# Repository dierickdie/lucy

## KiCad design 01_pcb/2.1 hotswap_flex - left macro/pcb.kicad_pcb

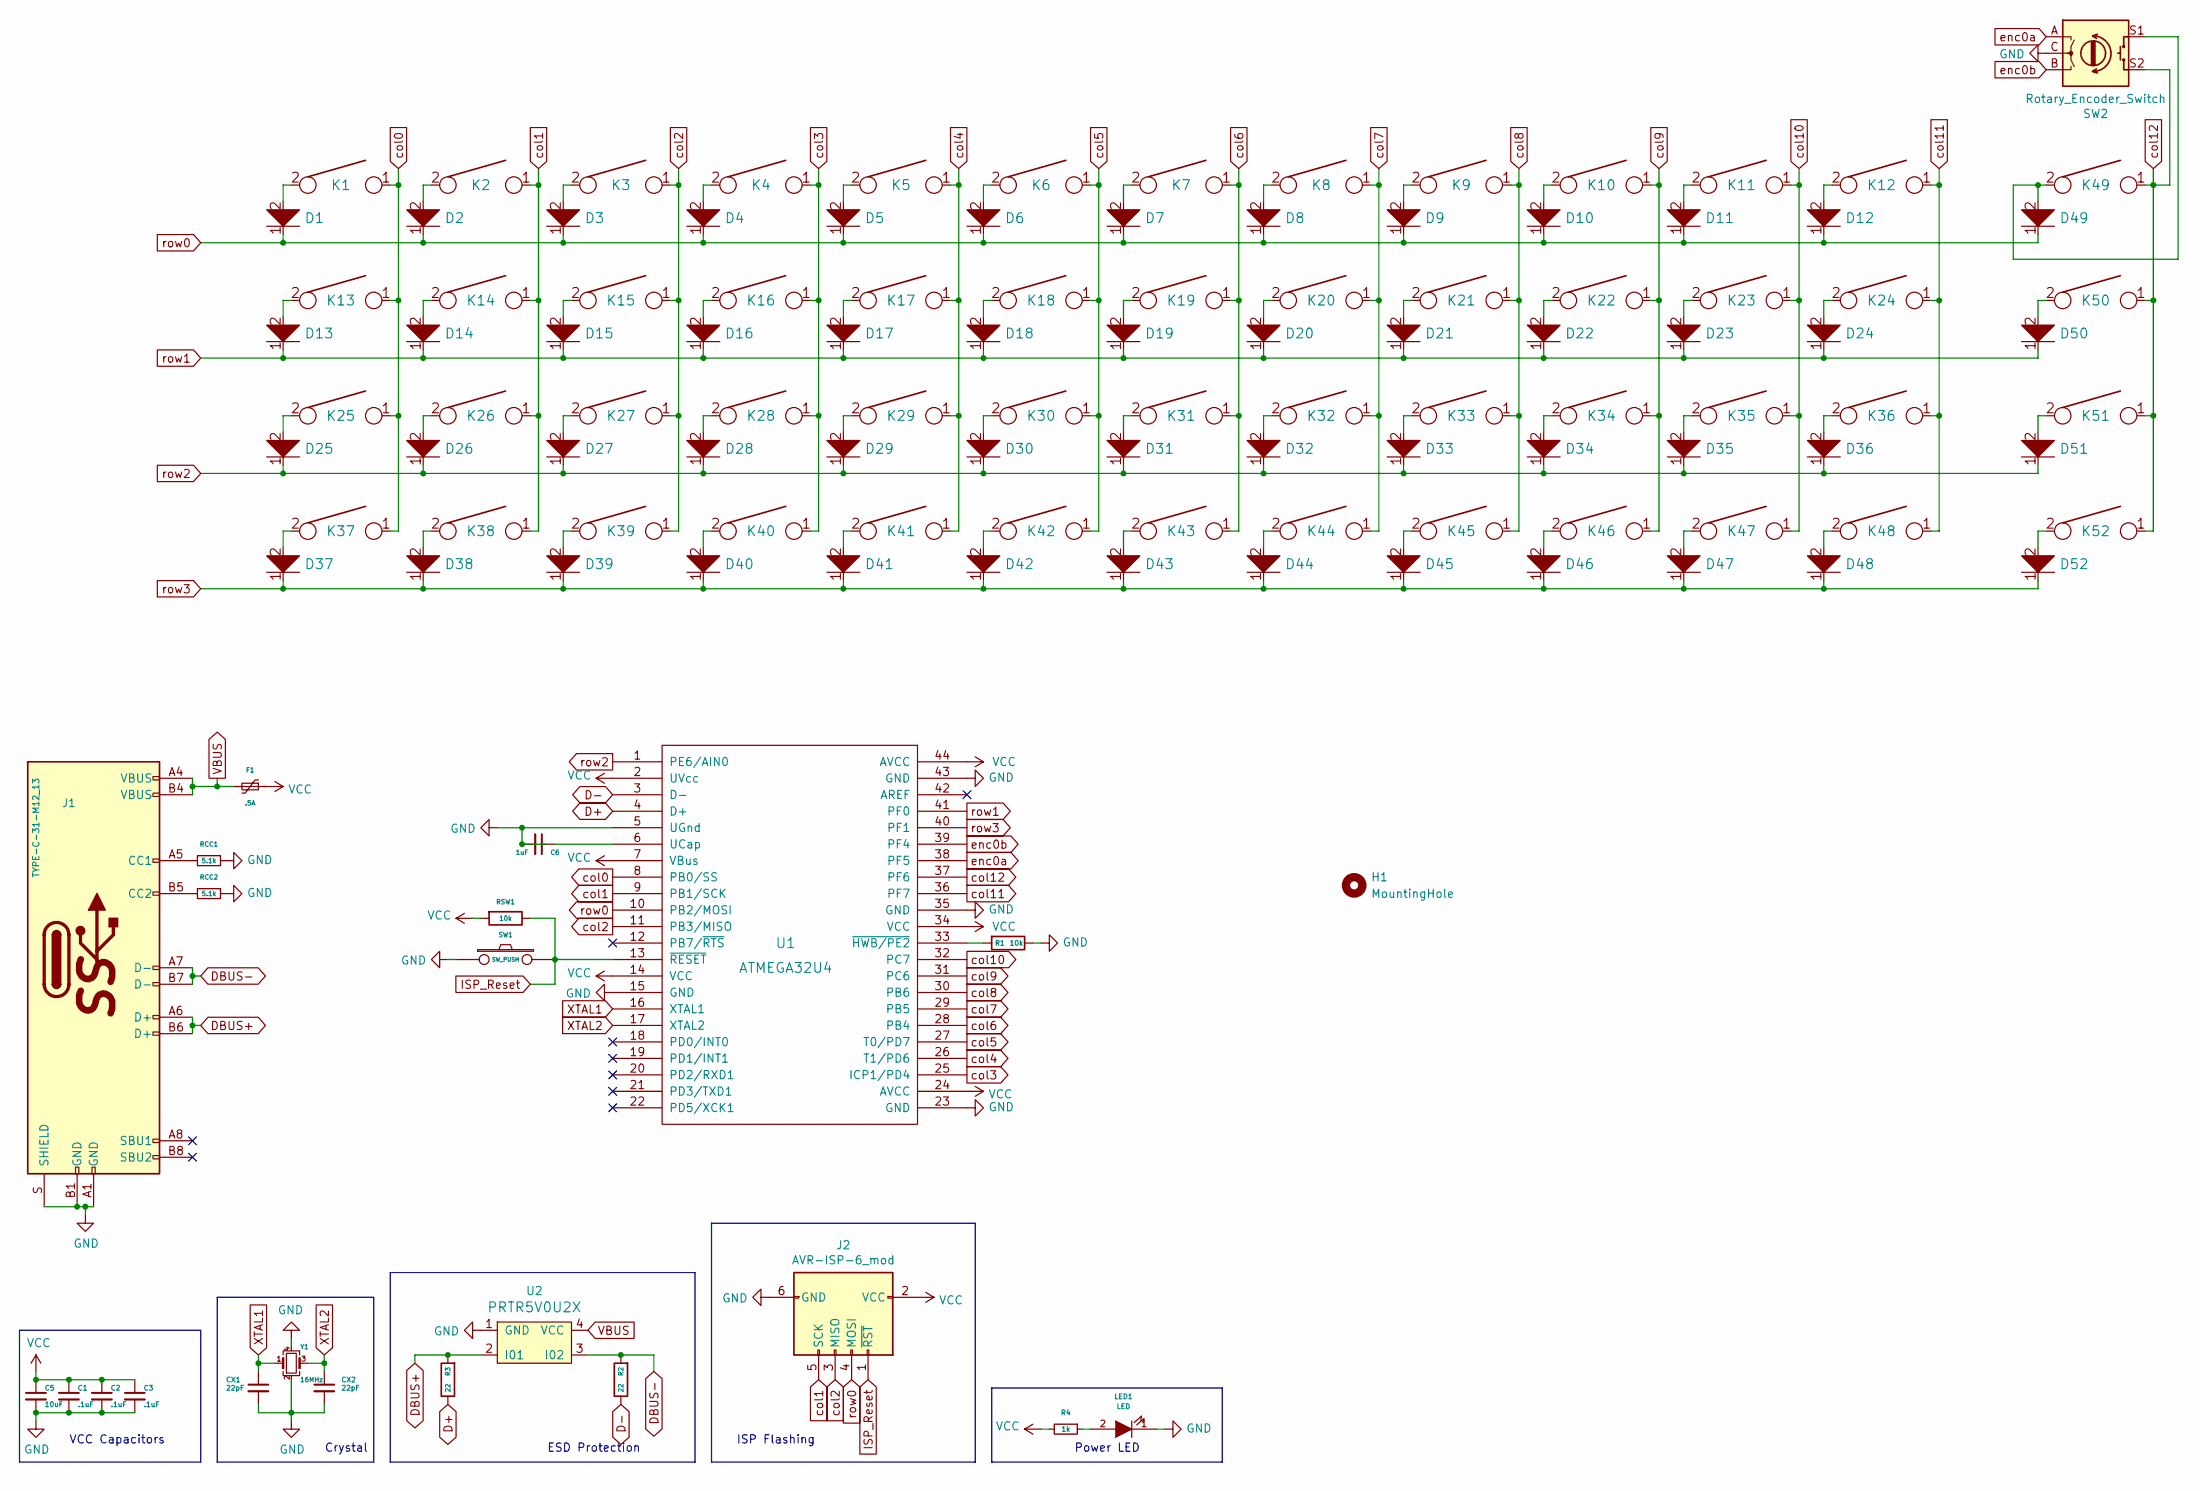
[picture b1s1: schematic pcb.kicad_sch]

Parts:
C1: .1uF; C_0805_2012Metric_Pad1.18x1.45mm_HandSolder
C2, C3: .1uF; C_0805_2012Metric_Pad1.15x1.40mm_HandSolder
C5: 10uF; C_0805_2012Metric_Pad1.15x1.40mm_HandSolder
C6: 1uF; C_0805_2012Metric_Pad1.15x1.40mm_HandSolder
CX1, CX2: 22pF; C_0805_2012Metric_Pad1.15x1.40mm_HandSolder
D1, D2, D3, D4, D5, D6, D7, D8, D9, D10, D11, D12, D13, D14, D15, D16, D17, D18, D19, D20, D21, D22, D23, D24, D25, D26, D27, D28, D29, D30, D31, D32, D33, D34, D35, D36, D37, D38, D39, D40, D41, D42, D43, D44, D45, D46, D47, D48, D49, D50, D51, D52: D; D_SOD-123_modified
F1: .5A; Fuse_0805_2012Metric_Pad1.15x1.40mm_HandSolder
H1: MountingHole; MountingHole_2.2mm_M2_DIN965_Pad
J1: TYPE-C-31-M12_13; TYPE-C-31-M-12
J2: AVR-ISP-6_mod; ICSP-Header
K1, K2, K3, K4, K5, K6, K7, K8, K9, K10, K11, K12, K13, K14, K15, K16, K17, K18, K19, K20, K21, K22, K23, K24, K25, K26, K27, K28, K29, K30, K31, K32, K33, K34, K35, K36, K37, K38, K39, K40, K41, K42, K43, K44, K45, K46, K47, K48, K49, K50, K51, K52: KEYSW; MX100
LED1: LED; LED_0805_2012Metric_Pad1.15x1.40mm_HandSolder
R1: 10k; R_0805_2012Metric_Pad1.15x1.40mm_HandSolder
R2, R3: 22; R_0805_2012Metric_Pad1.15x1.40mm_HandSolder
R4: 1k; R_0805_2012Metric_Pad1.15x1.40mm_HandSolder
RCC1, RCC2: 5.1k; R_0805_2012Metric_Pad1.15x1.40mm_HandSolder
RSW1: 10k; R_0805_2012Metric_Pad1.15x1.40mm_HandSolder
SW1: SW_PUSH; SKQG-1155865
SW2: Rotary_Encoder_Switch; RotaryEncoder_EC11
U1: ATMEGA32U4; ATMEGA32U4-AU
U2: PRTR5V0U2X; SOT-143B
Y1: 16MHz; Crystal_SMD_3225-4Pin_3.2x2.5mm_HandSoldering

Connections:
D+: R3.1, U1.4 (D+); also elsewhere on the board
D-: R2.1, U1.3 (D-); also elsewhere on the board
DBUS+: J1.A6 (D+), J1.B6 (D+), R3.2, U2.2 (I01)
DBUS-: J1.A7 (D-), J1.B7 (D-), R2.2, U2.3 (I02)
GND: C1.2, C2.2, C3.2, C5.2, C6.2, CX1.2, CX2.2, J1.A1 (GND), J1.B1 (GND), J1.S (SHIELD), J2.6 (GND), LED1.1 (K), R1.1, RCC1.1, RCC2.1, SW1.1, SW2.C, U1.5 (UGnd), U1.15 (GND), U1.23 (GND), U1.35 (GND), U1.43 (GND), U2.1 (GND), Y1.2, Y1.4; also elsewhere on the board
ISP_Reset: J2.1 (~RST), RSW1.1, SW1.2, U1.13 (~RESET)
unnamed: C6.1, U1.6 (UCap)
unnamed: D1.2, K1.2
unnamed: D2.2, K2.2
unnamed: D3.2, K3.2
unnamed: D4.2, K4.2
unnamed: D5.2, K5.2
unnamed: D6.2, K6.2
unnamed: D7.2, K7.2
unnamed: D8.2, K8.2
unnamed: D9.2, K9.2
unnamed: D10.2, K10.2
unnamed 17: D11.2, K11.2; also elsewhere on the board
unnamed: D12.2, K12.2
unnamed: D13.2, K13.2
unnamed: D14.2, K14.2
unnamed: D15.2, K15.2
unnamed: D16.2, K16.2
unnamed: D17.2, K17.2
unnamed: D18.2, K18.2
unnamed: D19.2, K19.2
unnamed: D20.2, K20.2
unnamed: D21.2, K21.2
unnamed 28: D22.2, K22.2; also elsewhere on the board
unnamed: D23.2, K23.2
unnamed: D24.2, K24.2
unnamed: D25.2, K25.2
unnamed: D26.2, K26.2
unnamed: D27.2, K27.2
unnamed: D28.2, K28.2
unnamed: D29.2, K29.2
unnamed: D30.2, K30.2
unnamed: D31.2, K31.2
unnamed: D32.2, K32.2
unnamed: D33.2, K33.2
unnamed: D34.2, K34.2
unnamed 41: D35.2, K35.2; also elsewhere on the board
unnamed: D36.2, K36.2
unnamed: D37.2, K37.2
unnamed: D38.2, K38.2
unnamed: D39.2, K39.2
unnamed 46: D40.2, K40.2; also elsewhere on the board
unnamed 47: D41.2, K41.2; also elsewhere on the board
unnamed: D42.2, K42.2
unnamed: D43.2, K43.2
unnamed: D44.2, K44.2
unnamed: D45.2, K45.2
unnamed: D46.2, K46.2
unnamed: D47.2, K47.2
unnamed: D48.2, K48.2
unnamed: D49.2, K49.2, SW2.S1
unnamed: D50.2, K50.2
unnamed: D51.2, K51.2
unnamed: D52.2, K52.2
unnamed: J1.A5 (CC1), RCC1.2
unnamed: J1.B5 (CC2), RCC2.2
unnamed 61: U1.18 (PD0/INT0); also elsewhere on the board
unnamed 62: U1.19 (PD1/INT1); also elsewhere on the board
unnamed 63: U1.20 (PD2/RXD1); also elsewhere on the board
unnamed 64: U1.21 (PD3/TXD1); also elsewhere on the board
unnamed 65: U1.22 (PD5/XCK1); also elsewhere on the board
unnamed: LED1.2 (A), R4.1
unnamed: R1.2, U1.33 (~HWB/PE2)
VBUS: F1.2, J1.A4 (VBUS), J1.B4 (VBUS), U2.4 (VCC)
VCC: C1.1, C2.1, C3.1, C5.1, F1.1, J2.2 (VCC), R4.2, RSW1.2, U1.2 (UVcc), U1.7 (VBus), U1.14 (VCC), U1.24 (AVCC), U1.34 (VCC), U1.44 (AVCC); also elsewhere on the board
XTAL1: CX1.1, U1.16 (XTAL1), Y1.1
XTAL2: CX2.1, U1.17 (XTAL2), Y1.3
col0: K1.1, K13.1, K25.1, K37.1, U1.8 (PB0/SS)
col1: J2.5 (SCK), K2.1, K14.1, K26.1, K38.1, U1.9 (PB1/SCK)
col2: J2.3 (MISO), K3.1, K15.1, K27.1, K39.1, U1.11 (PB3/MISO)
col3: K4.1, K16.1, K28.1, K40.1, U1.25 (ICP1/PD4); also elsewhere on the board
col4: K5.1, K17.1, K29.1, K41.1, U1.26 (T1/PD6); also elsewhere on the board
col5: K6.1, K18.1, K30.1, K42.1, U1.27 (T0/PD7)
col6: K7.1, K19.1, K31.1, K43.1, U1.28 (PB4)
col7: K8.1, K20.1, K32.1, K44.1, U1.29 (PB5)
col8: K9.1, K21.1, K33.1, K45.1, U1.30 (PB6)
col9: K10.1, K22.1, K34.1, K46.1, U1.31 (PC6); also elsewhere on the board
col10: K11.1, K23.1, K35.1, K47.1, U1.32 (PC7); also elsewhere on the board
col11: K12.1, K24.1, K36.1, K48.1, U1.36 (PF7)
col12: K49.1, K50.1, K51.1, K52.1, SW2.S2, U1.37 (PF6)
enc0a: SW2.A, U1.38 (PF5)
enc0b: SW2.B, U1.39 (PF4)
row0: D1.1, D2.1, D3.1, D4.1, D5.1, D6.1, D7.1, D8.1, D9.1, D10.1, D11.1, D12.1, D49.1, J2.4 (MOSI), U1.10 (PB2/MOSI)
row1: D13.1, D14.1, D15.1, D16.1, D17.1, D18.1, D19.1, D20.1, D21.1, D22.1, D23.1, D24.1, D50.1, U1.41 (PF0)
row2: D25.1, D26.1, D27.1, D28.1, D29.1, D30.1, D31.1, D32.1, D33.1, D34.1, D35.1, D36.1, D51.1, U1.1 (PE6/AIN0)
row3: D37.1, D38.1, D39.1, D40.1, D41.1, D42.1, D43.1, D44.1, D45.1, D46.1, D47.1, D48.1, D52.1, U1.40 (PF1)

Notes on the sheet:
ESD Protection
Crystal
Power LED
VCC Capacitors
ISP Flashing

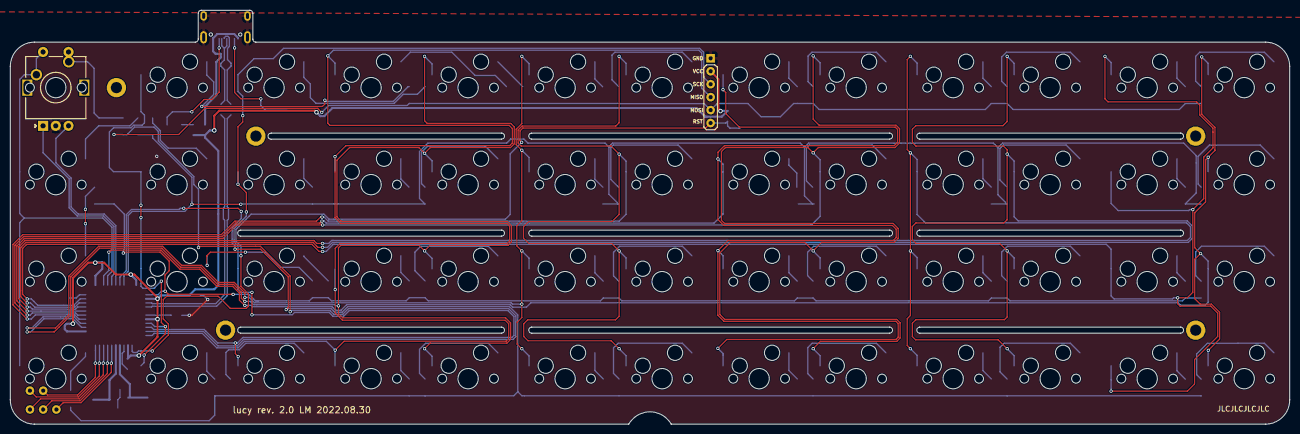
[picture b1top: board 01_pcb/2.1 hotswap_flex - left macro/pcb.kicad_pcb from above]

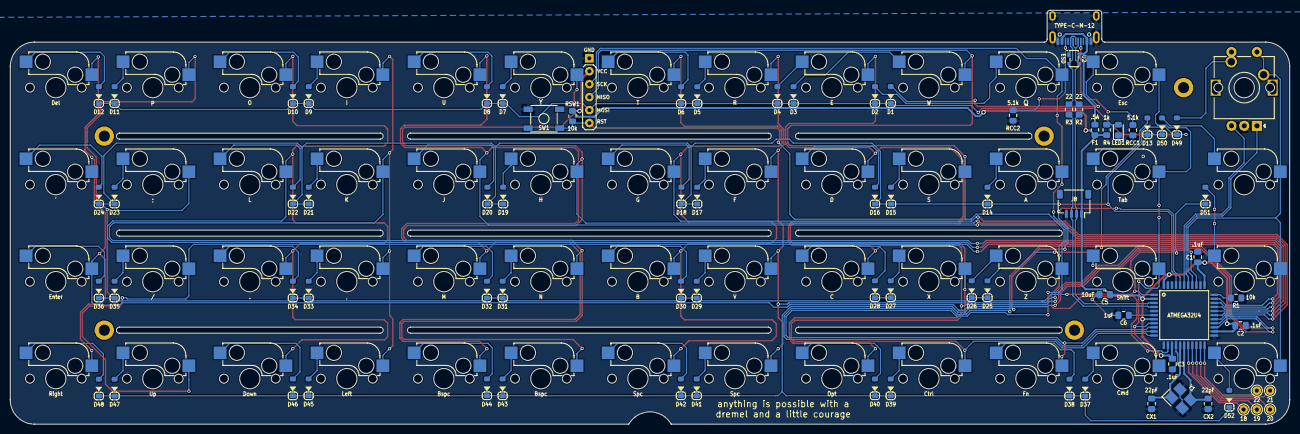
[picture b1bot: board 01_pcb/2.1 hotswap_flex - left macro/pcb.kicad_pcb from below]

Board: 2 copper layers, 251.2 x 81.3 mm, 138 parts (80 on the bottom side), 91 nets.

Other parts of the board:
H2, H3, H4, H5: MountingHole; MountingHole_2.2mm_M2_DIN965_Pad
J3, J4, J5, J6, J7: Conn_01x01; TestPoint_Keystone_5000-5004_Miniature
J8: 4PIN; JST_SH_SM04B-SRSS-TB_1x04-1MP_P1.00mm_Horizontal
locked: KEYSW; MXOnly-1U-Hotswap
locked#2, locked#3, locked#4, locked#5: KEYSW; MXOnly-1U-Hotswap

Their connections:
D+: J8.3; also elsewhere on the board
D-: J8.2; also elsewhere on the board
GND: J8.4; also elsewhere on the board
unnamed 17: locked.2; also elsewhere on the board
unnamed 28: locked#5.2; also elsewhere on the board
unnamed 41: locked#4.2; also elsewhere on the board
unnamed 46: locked#2.2; also elsewhere on the board
unnamed 47: locked#3.2; also elsewhere on the board
unnamed 61: J3.1; also elsewhere on the board
unnamed 62: J4.1; also elsewhere on the board
unnamed 63: J5.1; also elsewhere on the board
unnamed 64: J6.1; also elsewhere on the board
unnamed 65: J7.1; also elsewhere on the board
VCC: J8.1; also elsewhere on the board
col3: locked#2.1; also elsewhere on the board
col4: locked#3.1; also elsewhere on the board
col9: locked#5.1; also elsewhere on the board
col10: locked.1, locked#4.1; also elsewhere on the board

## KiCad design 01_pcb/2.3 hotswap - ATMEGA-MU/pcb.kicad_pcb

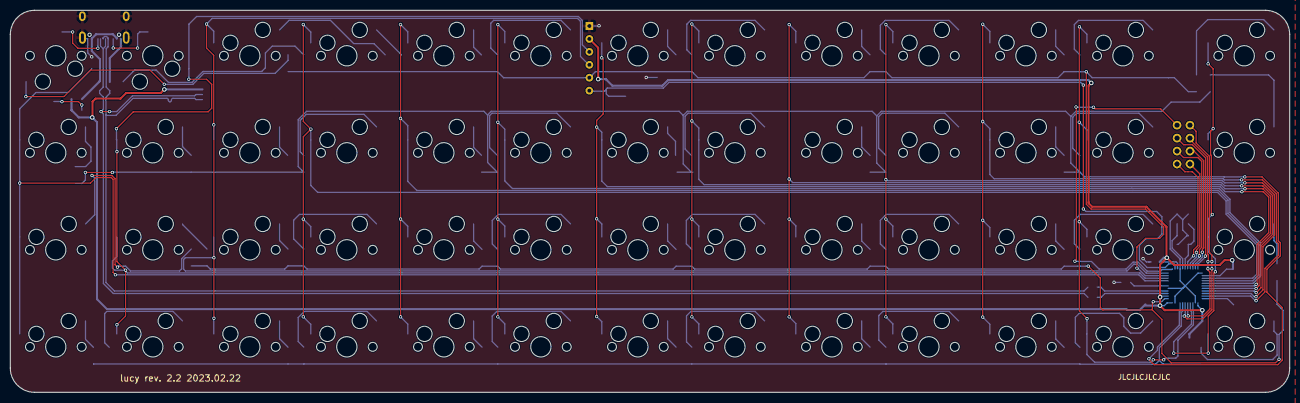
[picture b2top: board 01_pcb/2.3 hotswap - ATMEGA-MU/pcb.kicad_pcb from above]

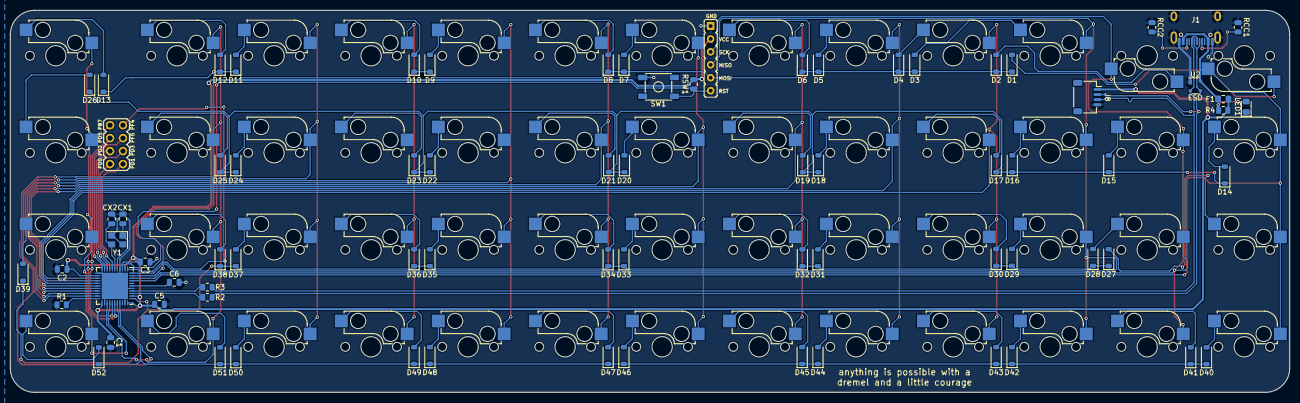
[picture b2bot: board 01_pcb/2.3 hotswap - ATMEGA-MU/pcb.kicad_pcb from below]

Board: 2 copper layers, 251.2 x 75.0 mm, 128 parts (76 on the bottom side), 92 nets.

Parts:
C1, C2, C3: .1uF; C_0805_2012Metric
C5: 10uF; C_0805_2012Metric
C6: 1uF; C_0805_2012Metric
CX1, CX2: 22pF; C_0805_2012Metric
D1, D2, D3, D4, D5, D6, D7, D8, D9, D10, D11, D12, D13, D14, D15, D16, D17, D18, D19, D20, D21, D22, D23, D24, D25, D26, D27, D28, D29, D30, D31, D32, D33, D34, D35, D36, D37, D38, D39, D40, D41, D42, D43, D44, D45, D46, D47, D48, D49, D50, D51, D52: D_Small; D_SOD-123
F1: .5A; Fuse_0805_2012Metric_Pad1.15x1.40mm_HandSolder
J1: TYPE-C-31-M12_13; TYPE-C-31-M-12
J2: AVR-ISP-6_mod; PinHeader_1x6_P2.54mm_Vertical
J3: Conn_01x08; PinHeader_2x04_P2.54mm_Vertical
J8: 4PIN; JST_SH_SM04B-SRSS-TB_1x04-1MP_P1.00mm_Horizontal
LED1: LED; LED_0805_2012Metric_Pad1.15x1.40mm_HandSolder
MX1, MX2, MX3, MX4, MX5, MX6, MX7, MX8, MX9, MX10, MX12, MX13, MX14, MX15, MX16, MX17, MX18, MX19, MX20, MX21, MX22, MX24, MX25, MX26, MX27, MX28, MX29, MX30, MX31, MX32, MX33, MX34, MX35, MX36, MX38, MX39, MX40, MX41, MX42, MX45, MX46, MX47, MX48, MX49, MX50, MX51, MX52: MX-NoLED; MXOnly-1U-Hotswap
R1: 10k; R_0805_2012Metric
R2, R3: 22; R_0805_2012Metric
R4: 1k; R_0805_2012Metric
RCC1, RCC2: 5.1k; R_0805_2012Metric
RSW1: 10k; R_0805_2012Metric
SW1: SW_PUSH; SKQG-1155865
U2: PRTR5V0U2X; SOT-143
U3: ATmega32U4-M; QFN-44-1EP_7x7mm_P0.5mm_EP5.2x5.2mm
Y1: 16MHz; Crystal_SMD_3225-4Pin_3.2x2.5mm
locked: MX-NoLED; MXOnly-1U-Hotswap
locked#2, locked#3, locked#4, locked#5: MX-NoLED; MXOnly-1U-Hotswap

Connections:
D+: R3.1, U3.4 (D+)
D-: R2.1, U3.3 (D-)
DBUS+: J1.A6 (D+), J1.B6 (D+), J8.3, R3.2, U2.2 (I01)
DBUS-: J1.A7 (D-), J1.B7 (D-), J8.2, R2.2, U2.3 (I02)
GND: C1.2, C2.2, C3.2, C5.2, C6.2, CX1.2, CX2.2, J1.A1 (GND), J1.B1 (GND), J1.S (SHIELD), J2.6 (GND), J8.4, LED1.1 (K), R1.1, RCC1.1, RCC2.1, SW1.1, U2.1 (GND), U3.5 (UGND), U3.15 (GND), U3.23 (GND), U3.35 (GND), U3.43 (GND), U3.45 (GND), Y1.2, Y1.4
ISP_Reset: J2.1 (~RST), RSW1.1, SW1.2, U3.13 (~RESET)
unnamed: D1.2 (A), MX1.2 (ROW)
unnamed: D2.2 (A), MX2.2 (ROW)
unnamed: D3.2 (A), MX3.2 (ROW)
unnamed: D4.2 (A), MX4.2 (ROW)
unnamed: D5.2 (A), MX5.2 (ROW)
unnamed: D6.2 (A), MX6.2 (ROW)
unnamed: D7.2 (A), MX7.2 (ROW)
unnamed: D8.2 (A), MX8.2 (ROW)
unnamed: D9.2 (A), MX9.2 (ROW)
unnamed: D10.2 (A), MX10.2 (ROW)
unnamed: D11.2 (A), locked.2 (ROW)
unnamed: D12.2 (A), MX12.2 (ROW)
unnamed: D13.2 (A), MX13.2 (ROW)
unnamed: D14.2 (A), MX14.2 (ROW)
unnamed: D15.2 (A), MX15.2 (ROW)
unnamed: D16.2 (A), MX16.2 (ROW)
unnamed: D17.2 (A), MX17.2 (ROW)
unnamed: D18.2 (A), MX18.2 (ROW)
unnamed: D19.2 (A), MX19.2 (ROW)
unnamed: D20.2 (A), MX20.2 (ROW)
unnamed: D21.2 (A), MX21.2 (ROW)
unnamed: D22.2 (A), MX22.2 (ROW)
unnamed: D23.2 (A), locked#5.2 (ROW)
unnamed: D24.2 (A), MX24.2 (ROW)
unnamed: D25.2 (A), MX25.2 (ROW)
unnamed: D26.2 (A), MX26.2 (ROW)
unnamed: D27.2 (A), MX27.2 (ROW)
unnamed: D28.2 (A), MX28.2 (ROW)
unnamed: D29.2 (A), MX29.2 (ROW)
unnamed: D30.2 (A), MX30.2 (ROW)
unnamed: D31.2 (A), MX31.2 (ROW)
unnamed: D32.2 (A), MX32.2 (ROW)
unnamed: D33.2 (A), MX33.2 (ROW)
unnamed: D34.2 (A), MX34.2 (ROW)
unnamed: D35.2 (A), MX35.2 (ROW)
unnamed: D36.2 (A), MX36.2 (ROW)
unnamed: D37.2 (A), locked#4.2 (ROW)
unnamed: D38.2 (A), MX38.2 (ROW)
unnamed: D39.2 (A), MX39.2 (ROW)
unnamed: D40.2 (A), MX40.2 (ROW)
unnamed: D41.2 (A), MX41.2 (ROW)
unnamed: D42.2 (A), MX42.2 (ROW)
unnamed: D43.2 (A), locked#2.2 (ROW)
unnamed: D44.2 (A), locked#3.2 (ROW)
unnamed: D45.2 (A), MX45.2 (ROW)
unnamed: D46.2 (A), MX46.2 (ROW)
unnamed: D47.2 (A), MX47.2 (ROW)
unnamed: D48.2 (A), MX48.2 (ROW)
unnamed: D49.2 (A), MX49.2 (ROW)
unnamed: D50.2 (A), MX50.2 (ROW)
unnamed: D51.2 (A), MX51.2 (ROW)
unnamed: D52.2 (A), MX52.2 (ROW)
unnamed: J1.A5 (CC1), RCC1.2
unnamed: J1.B5 (CC2), RCC2.2
unnamed: LED1.2 (A), R4.1
unnamed: C6.1, U3.6 (UCAP)
unnamed: R1.2, U3.33 (~HWB/PE2)
VBUS: F1.2, J1.A4 (VBUS), J1.B4 (VBUS), U2.4 (VCC)
VCC: C1.1, C2.1, C3.1, C5.1, F1.1, J2.2 (VCC), J8.1, R4.2, RSW1.2, U3.2 (UVCC), U3.14 (VCC), U3.24 (AVCC), U3.34 (VCC), U3.44 (AVCC)
XTAL1: CX2.1, U3.17 (XTAL1), Y1.3
XTAL2: CX1.1, U3.16 (XTAL2), Y1.1
col0: MX1.1 (COL), MX14.1 (COL), MX27.1 (COL), MX40.1 (COL), U3.8 (PB0)
col1/sck: J2.5 (SCK), MX2.1 (COL), MX15.1 (COL), MX28.1 (COL), MX41.1 (COL), U3.9 (PB1)
col2/miso: J2.3 (MISO), MX3.1 (COL), MX16.1 (COL), MX29.1 (COL), MX42.1 (COL), U3.11 (PB3)
col3: MX4.1 (COL), MX17.1 (COL), MX30.1 (COL), U3.25 (PD4), locked#2.1 (COL)
col4: MX5.1 (COL), MX18.1 (COL), MX31.1 (COL), U3.26 (PD6), locked#3.1 (COL)
col5: MX6.1 (COL), MX19.1 (COL), MX32.1 (COL), MX45.1 (COL), U3.27 (PD7)
col6: MX7.1 (COL), MX20.1 (COL), MX33.1 (COL), MX46.1 (COL), U3.28 (PB4)
col7: MX8.1 (COL), MX21.1 (COL), MX34.1 (COL), MX47.1 (COL), U3.29 (PB5)
col8: MX9.1 (COL), MX35.1 (COL), MX48.1 (COL), U3.30 (PB6)
col9: MX10.1 (COL), MX36.1 (COL), MX49.1 (COL), U3.31 (PC6)
col10: MX24.1 (COL), MX50.1 (COL), U3.32 (PC7), locked.1 (COL), locked#4.1 (COL)
col11: MX12.1 (COL), MX25.1 (COL), MX38.1 (COL), MX51.1 (COL), U3.36 (PF7)
col12: MX13.1 (COL), MX26.1 (COL), MX39.1 (COL), MX52.1 (COL), U3.37 (PF6)
extra1: J3.1, U3.39 (PF4)
extra2: J3.2, U3.12 (PB7)
extra3: J3.3, U3.38 (PF5)
extra4: J3.4, U3.22 (PD5)
extra5: J3.5, U3.21 (PD3)
extra6: J3.6, U3.20 (PD2)
extra7: J3.7, U3.19 (PD1)
extra8: J3.8, U3.18 (PD0)
row0/mosi: D1.1 (K), D2.1 (K), D3.1 (K), D4.1 (K), D5.1 (K), D6.1 (K), D7.1 (K), D8.1 (K), D9.1 (K), D10.1 (K), D11.1 (K), D12.1 (K), D13.1 (K), J2.4 (MOSI), U3.10 (PB2)
row1: D14.1 (K), D15.1 (K), D16.1 (K), D17.1 (K), D18.1 (K), D19.1 (K), D20.1 (K), D21.1 (K), D22.1 (K), D23.1 (K), D24.1 (K), D25.1 (K), D26.1 (K), U3.41 (PF0)
row2: D27.1 (K), D28.1 (K), D29.1 (K), D30.1 (K), D31.1 (K), D32.1 (K), D33.1 (K), D34.1 (K), D35.1 (K), D36.1 (K), D37.1 (K), D38.1 (K), D39.1 (K), U3.1 (PE6)
row3: D40.1 (K), D41.1 (K), D42.1 (K), D43.1 (K), D44.1 (K), D45.1 (K), D46.1 (K), D47.1 (K), D48.1 (K), D49.1 (K), D50.1 (K), D51.1 (K), D52.1 (K), U3.40 (PF1)
